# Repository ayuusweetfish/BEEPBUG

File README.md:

# BeepBug

*🚧 Final touches are work-in-progress, ETA spring 2024*

*BeepBug* is an interactive art installation, the thematic idea being that harmony between the artificial and the natural environment will supplant opposition.

The work comprises two sound-emitting cubes (or what could be perceived as shrubs), which aim to draw the audience’s attention to the delicate interconnections between naturality and artificiality. This central idea is manifested in intertextual relationships formed simultaneously in the auditory, the visual, and the cognitive domain.

## Current repository structure

- **flowerbed/**: The main hardware and firmware.
  - **hw/**: Hardware design for the sub units (sensor & microphone).
  - **hw_central/**: Hardware design for the main units (communication and synchronisation).
  - **fw_unit/**: Firmware for the sub units. (🚧)
- **testdrive/**: Various test & prototype implementations. Includes a crude Wizard-of-Oz implementation.

## Licence

Will switch to a proper CC licence at final release. Currently all rights reserved.

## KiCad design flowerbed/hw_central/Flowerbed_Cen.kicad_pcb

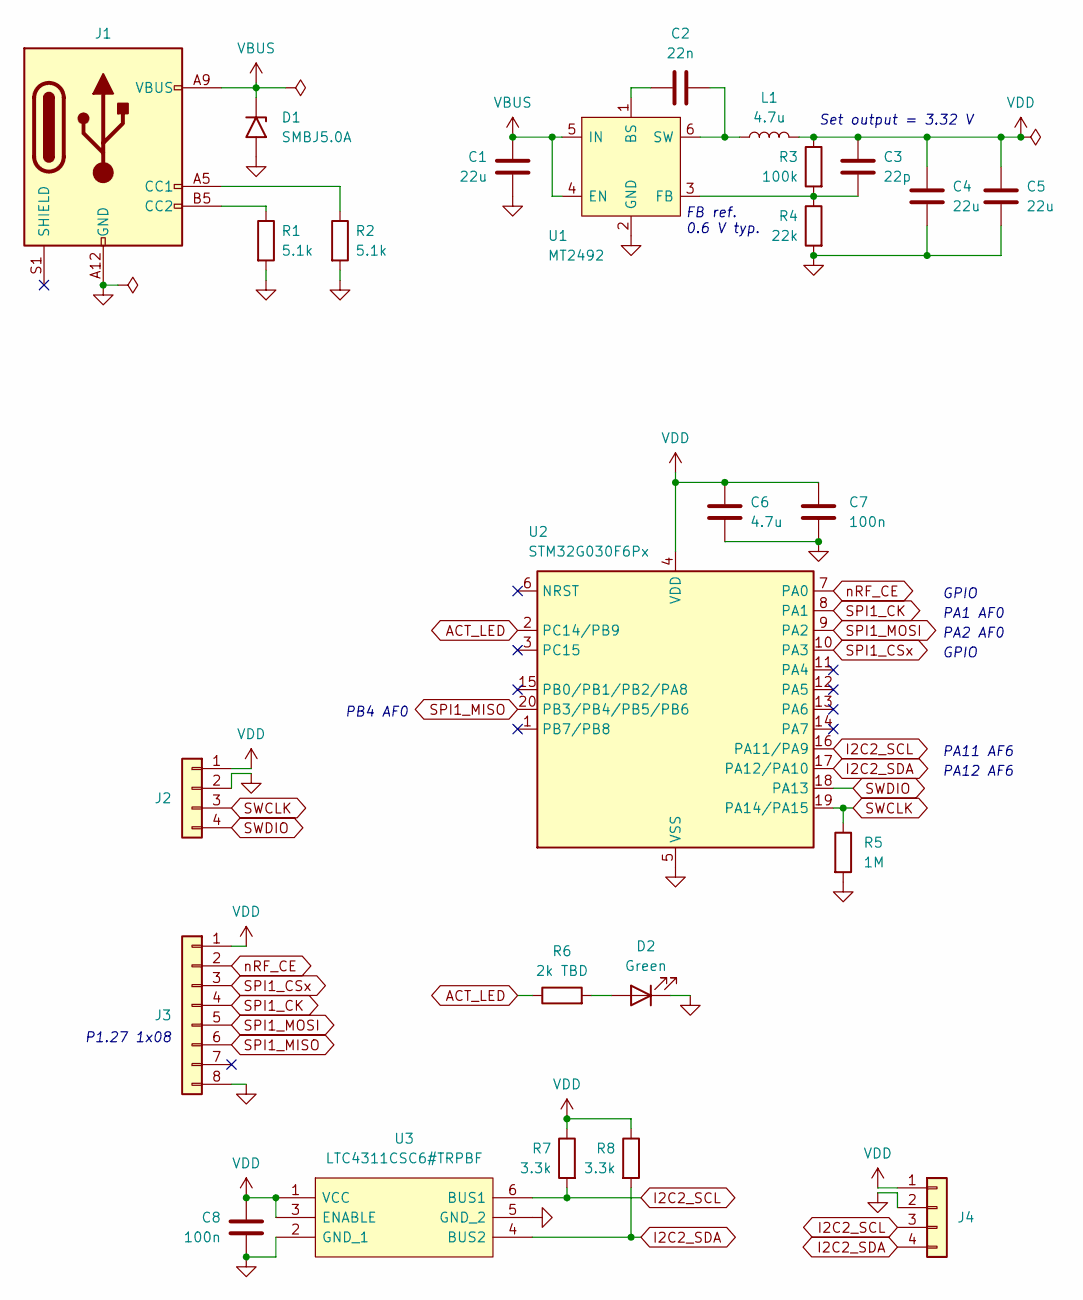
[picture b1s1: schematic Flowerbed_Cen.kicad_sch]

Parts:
C1, C4, C5: 22u; C_0603_1608Metric
C2: 22n; C_0603_1608Metric
C3: 22p; C_0603_1608Metric
C6: 4.7u; C_0603_1608Metric
C7, C8: 100n; C_0603_1608Metric
D1: SMBJ5.0A; D_SMB
D2: Green; LED_0603_1608Metric
J1: USB_C_Receptacle_PowerOnly_6P; USB_C_Receptacle
J2: Conn_01x04; TestPoints_1x04_P2.0
J3: Conn_01x08; SMD_Module_P1.27_1x08
J4: Conn_01x04; PinHeader_1x04_P2.54mm_Vertical
L1: 4.7u; L_Sunlord_MWSA1004S
R1, R2: 5.1k; R_0603_1608Metric
R3: 100k; R_0603_1608Metric
R4: 22k; R_0603_1608Metric
R5: 1M; R_0603_1608Metric
R6: 2k TBD; R_0603_1608Metric
R7, R8: 3.3k; R_0603_1608Metric
U1: MT2492; SOT-23-6; Manufacturer_Part_Number MT2492
U2: STM32G030F6Px; TSSOP-20_4.4x6.5mm_P0.65mm
U3: LTC4311CSC6#TRPBF; SOT65P210X100-6N; Manufacturer_Part_Number LTC4311CSC6#TRPBF; Mouser Part Number 584-LTC4311CSC6TRPBF

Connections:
ACT_LED: R6.1, U2.2 (PC14/PB9)
GND: C1.2, C4.2, C5.2, C6.2, C7.2, C8.2, D1.2 (A2), D2.1 (K), J1.A12 (GND), J1.B12 (GND), J2.2, J3.8, J4.2, R1.2, R2.2, R4.2, R5.2, U1.2 (GND), U2.5 (VSS), U3.2 (GND_1), U3.5 (GND_2)
I2C2_SCL: J4.3, R7.2, U2.16 (PA11/PA9), U3.6 (BUS1)
I2C2_SDA: J4.4, R8.2, U2.17 (PA12/PA10), U3.4 (BUS2)
unnamed: D2.2 (A), R6.2
unnamed: J1.A5 (CC1), R2.1
unnamed: J1.B5 (CC2), R1.1
unnamed: C2.1, U1.1 (BS)
unnamed: C3.2, R3.2, R4.1, U1.3 (FB)
unnamed: C2.2, L1.1, U1.6 (SW)
SPI1_CK: J3.4, U2.8 (PA1)
SPI1_CSx: J3.3, U2.10 (PA3)
SPI1_MISO: J3.6, U2.20 (PB3/PB4/PB5/PB6)
SPI1_MOSI: J3.5, U2.9 (PA2)
SWCLK: J2.3, R5.1, U2.19 (PA14/PA15)
SWDIO: J2.4, U2.18 (PA13)
VBUS: C1.1, D1.1 (A1), J1.A9 (VBUS), J1.B9 (VBUS), U1.4 (EN), U1.5 (IN)
VDD: C3.1, C4.1, C5.1, C6.1, C7.1, C8.1, J2.1, J3.1, J4.1, L1.2, R3.1, R7.1, R8.1, U2.4 (VDD), U3.1 (VCC), U3.3 (ENABLE)
nRF_CE: J3.2, U2.7 (PA0)

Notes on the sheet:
P1.27 1x08
PA1 AF0
PA11 AF6
PA2 AF0
GPIO
Set output = 3.32 V
PA12 AF6
PB4 AF0
FB ref. 0.6 V typ.

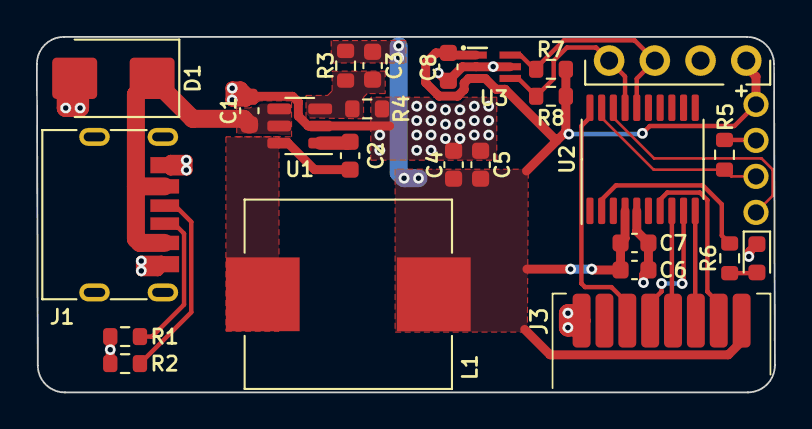
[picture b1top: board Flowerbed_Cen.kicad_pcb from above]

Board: 2 copper layers, 41.0 x 19.8 mm, 26 parts (0 on the bottom side), 19 nets.

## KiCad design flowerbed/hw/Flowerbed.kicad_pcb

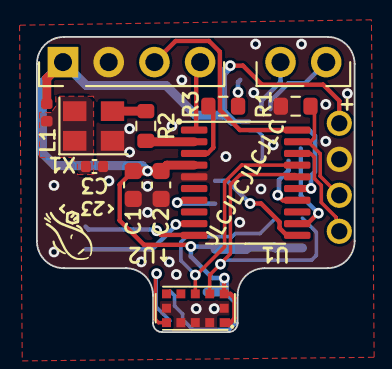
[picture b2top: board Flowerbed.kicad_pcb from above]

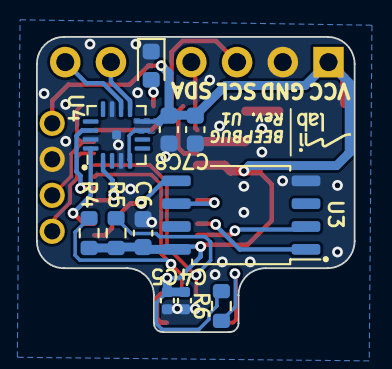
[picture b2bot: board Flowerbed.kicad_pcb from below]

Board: 2 copper layers, 17.7 x 16.4 mm, 24 parts (11 on the bottom side), 23 nets.

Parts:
C1: 4.7u; C_0603_1608Metric
C2, C6, C8: 100n; C_0603_1608Metric
C3, C5: 100n; C_0402_1005Metric
C4: 4.7u; C_0402_1005Metric
C7: 10u; C_0603_1608Metric
D1: Green; LED_0603_1608Metric
J1: Conn_01x04; PinHeader_1x04_P2.54mm_Vertical
J2: Conn_01x04; TestPoints_1x04_P2.0
L1: 10n; L_0402_1005Metric
LS1: Speaker; PinHeader_1x02_P2.54mm_Vertical
R1: 1M; R_0603_1608Metric
R2: 0 TBD; R_0603_1608Metric
R3: 2k TBD; R_0603_1608Metric
R4, R5: 2k; R_0603_1608Metric
R6: 10k; R_0603_1608Metric
U1: STM32G030F6Px; TSSOP-20_4.4x6.5mm_P0.65mm
U2: VL53L0X
U3: W25Q16JVSS; SOIC-8_5.23x5.23mm_P1.27mm
U4: MAX98357AETE+; QFN-16_3x3mm_P0.5mm
X1: 12.288MHz; Oscillator_SMD_Abracon_ASE-4Pin_3.2x2.5mm

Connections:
ACT_LED: R3.1, U1.3 (PC15)
GND: C1.2, C2.2, C3.2, C4.2, C5.2, C6.2, C7.2, C8.2, D1.1 (K), J1.2, J2.2, R1.2, U1.5 (VSS), U2.2 (AVSSVCSEL), U2.3 (GND), U2.4 (GND2), U2.6 (GND3), U2.12 (GND4), U3.4 (GND), U4.3 (GND_1), U4.11 (GND_2), U4.15 (GND_3), U4.17 (GND_4), X1.2 (GND)
I2C1_SCL: J1.3, U1.20 (PB3/PB4/PB5/PB6)
I2C1_SDA: J1.4, U1.1 (PB7/PB8)
I2C2_SCL: R4.2, U1.16 (PA11/PA9), U2.10 (SCL)
I2C2_SDA: R5.2, U1.17 (PA12/PA10), U2.9 (SDA)
I2S1_CK: U1.12 (PA5), U4.16 (BCLK)
I2S1_SD: U1.14 (PA7), U4.1 (DIN)
I2S1_WS: U1.15 (PB0/PB1/PB2/PA8), U4.14 (LRCLK)
unnamed: D1.2 (A), R3.2
unnamed: R2.2, U1.2 (PC14/PB9)
unnamed: R6.2, U2.5 (XSHUT)
unnamed: LS1.1, U4.10 (OUTN)
unnamed: LS1.2, U4.9 (OUTP)
unnamed: C3.1, L1.2, X1.1 (EN), X1.4 (Vdd)
unnamed: R2.1, X1.3 (OUT)
SPI2_CSx: U1.9 (PA2), U3.1 (~CS)
SPI2_MISO: U1.10 (PA3), U3.2 (DO(IO1))
SPI2_MOSI: U1.11 (PA4), U3.5 (DI(IO0))
SPI2_SCK: U1.7 (PA0), U3.6 (CLK)
SWCLK: J2.3, R1.1, U1.19 (PA14/PA15)
SWDIO: J2.4, U1.18 (PA13)
VDD: C1.1, C2.1, C4.1, C5.1, C6.1, C7.1, C8.1, J1.1, J2.1, L1.1, R4.1, R5.1, R6.1, U1.4 (VDD), U2.1 (AVDDVCSEL), U2.11 (AVDD), U3.8 (VCC), U4.4 (~SD_MODE), U4.7 (VDD_1), U4.8 (VDD_2)

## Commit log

2024-01-01 Electromagnet test-drive
2024-01-01 (WIP) Wizard of Oz framework
2024-01-01 Finish Wizard of Oz prototype
2024-01-02 Switch Oz from distributed Deno Deploy to WLAN server
2024-01-03 Adjust PWM duty cycle; confirm electromagnet characteristics
    The electromagnet is bistable; i.e. is not easily released once in the activated position. It is thus unsuitable for precision position control.
2024-01-04 Create circuit board for flowerbed units
2024-01-04 Flowerbed unit layout?
2024-01-04 Revise flowerbed unit layout
2024-01-04 (WIP) Add flowerbed central schematic
2024-01-05 Route flowerbed unit (!)
2024-01-05 Finalize flowerbed unit PCB design
2024-01-05 Finish flowerbed central schematic
2024-01-06 Finish flowerbed central board; submit for fab
2024-01-11 Blinking LED on unit hardware
2024-01-11 Verify HSE clock
2024-01-11 Enable PLL
2024-01-11 Verify VL53L0X I2C communication
2024-01-11 VL53L0X read-outs
2024-01-11 Commit VL53L0X API library into repo
2024-01-11 Adjust VL53L0X serial comm. timings
2024-01-11 Blast I2S data
2024-01-11 I2S through DMA circular/double buffer
2024-01-11 Communicating with flash
2024-01-11 Read flash with DMA
2024-01-11 Use combined IRQ lines for SPI DMA TX/RX
2024-01-12 Write files to flash
2024-01-12 Various debug scaffolding
2024-01-12 Correctly decode audio samples
2024-01-12 Play out audio
2024-01-12 Output stereo instead of 2x-sped-up mono
2024-01-12 Expose a subroutine for starting playback
2024-01-12 Signal mechanism in playback to prevent fleeting glitches
2024-01-12 Fade audio according to ToF sensor read-outs
2024-01-12 Seamless audio loops
2024-01-12 Add "Beep" variant
2024-01-14 Add README and figures
2024-01-14 Update README with repo structure and licensing
